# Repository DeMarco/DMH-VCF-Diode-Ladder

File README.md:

# DMH-VCF-Diode-Ladder

Voltage Controlled Filter module based on the design by Moritz Klein

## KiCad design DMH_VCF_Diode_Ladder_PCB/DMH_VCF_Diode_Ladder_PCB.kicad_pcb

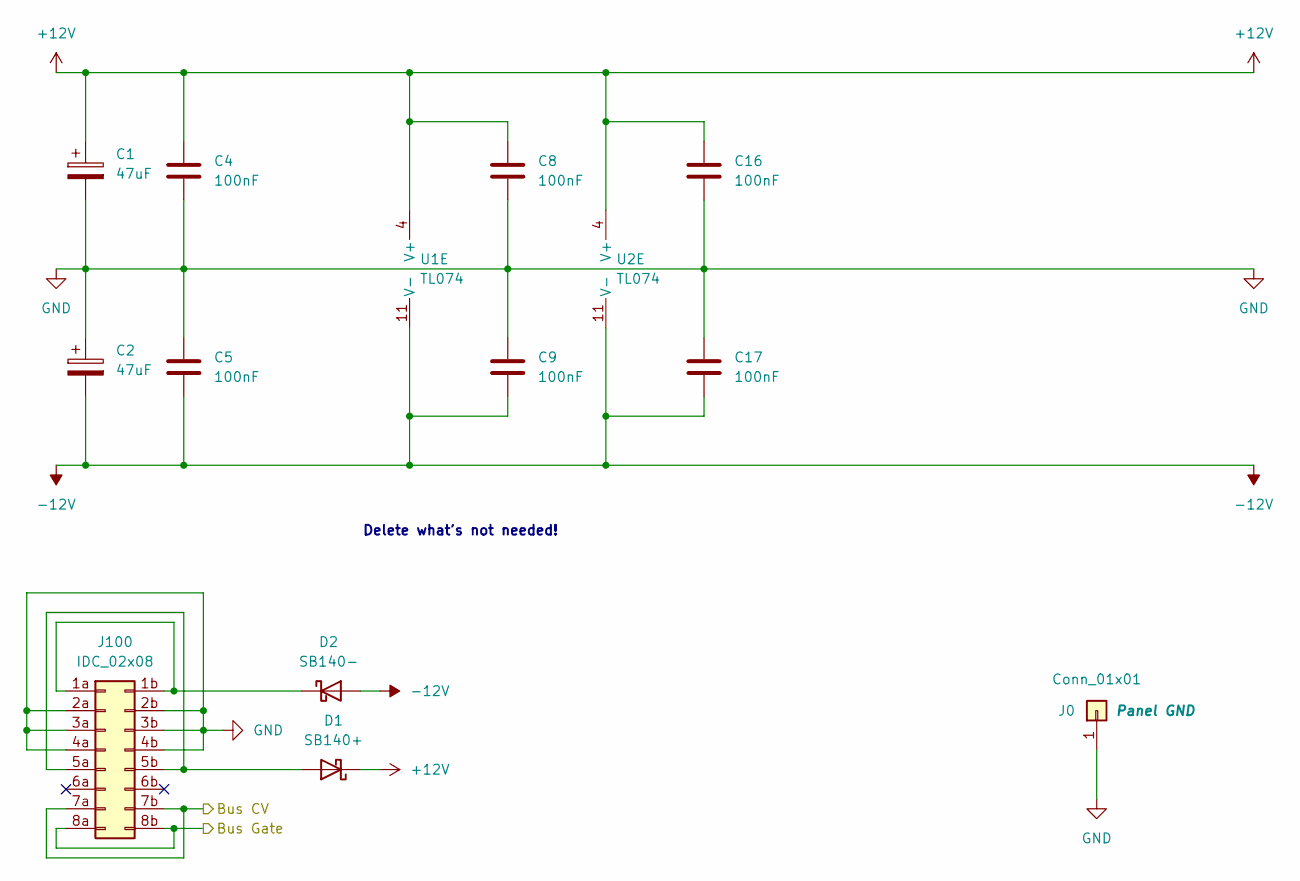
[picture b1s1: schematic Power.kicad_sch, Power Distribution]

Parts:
C1, C2: 47uF; CP_Radial_D5.0mm_P2.00mm
C4, C5, C8, C9, C16, C17: 100nF; C_Disc_D4.3mm_W1.9mm_P5.00mm
D1: SB140+; D_DO-41_SOD81_P10.16mm_Horizontal
D2: SB140-; D_DO-41_SOD81_P10.16mm_Horizontal
J0: Conn_01x01; PinHeader_1x01_P2.54mm_Vertical
J100: IDC_02x08; IDC-Header_2x08_P2.54mm_Vertical_Eurorack
U1, U2: TL074; DIP-14_W7.62mm_Socket

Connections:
+12V: C1.1, C4.1, C8.1, C16.1, D1.1 (K), U1.4 (V+), U2.4 (V+); also elsewhere on the board
-12V: C2.2, C5.2, C9.2, C17.2, D2.2 (A), U1.11 (V-), U2.11 (V-); also elsewhere on the board
/Inputs and Outputs/Bus CV In: J100.7a, J100.7b; also elsewhere on the board
/Power/Bus Gate: J100.8a, J100.8b
GND: C1.2, C2.1, C4.2, C5.1, C8.2, C9.1, C16.2, C17.1, J0.1, J100.2a, J100.2b, J100.3a, J100.3b, J100.4a, J100.4b; also elsewhere on the board
unnamed: D1.2 (A), J100.5a, J100.5b
unnamed: D2.1 (K), J100.1a, J100.1b

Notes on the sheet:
Delete what's not needed!

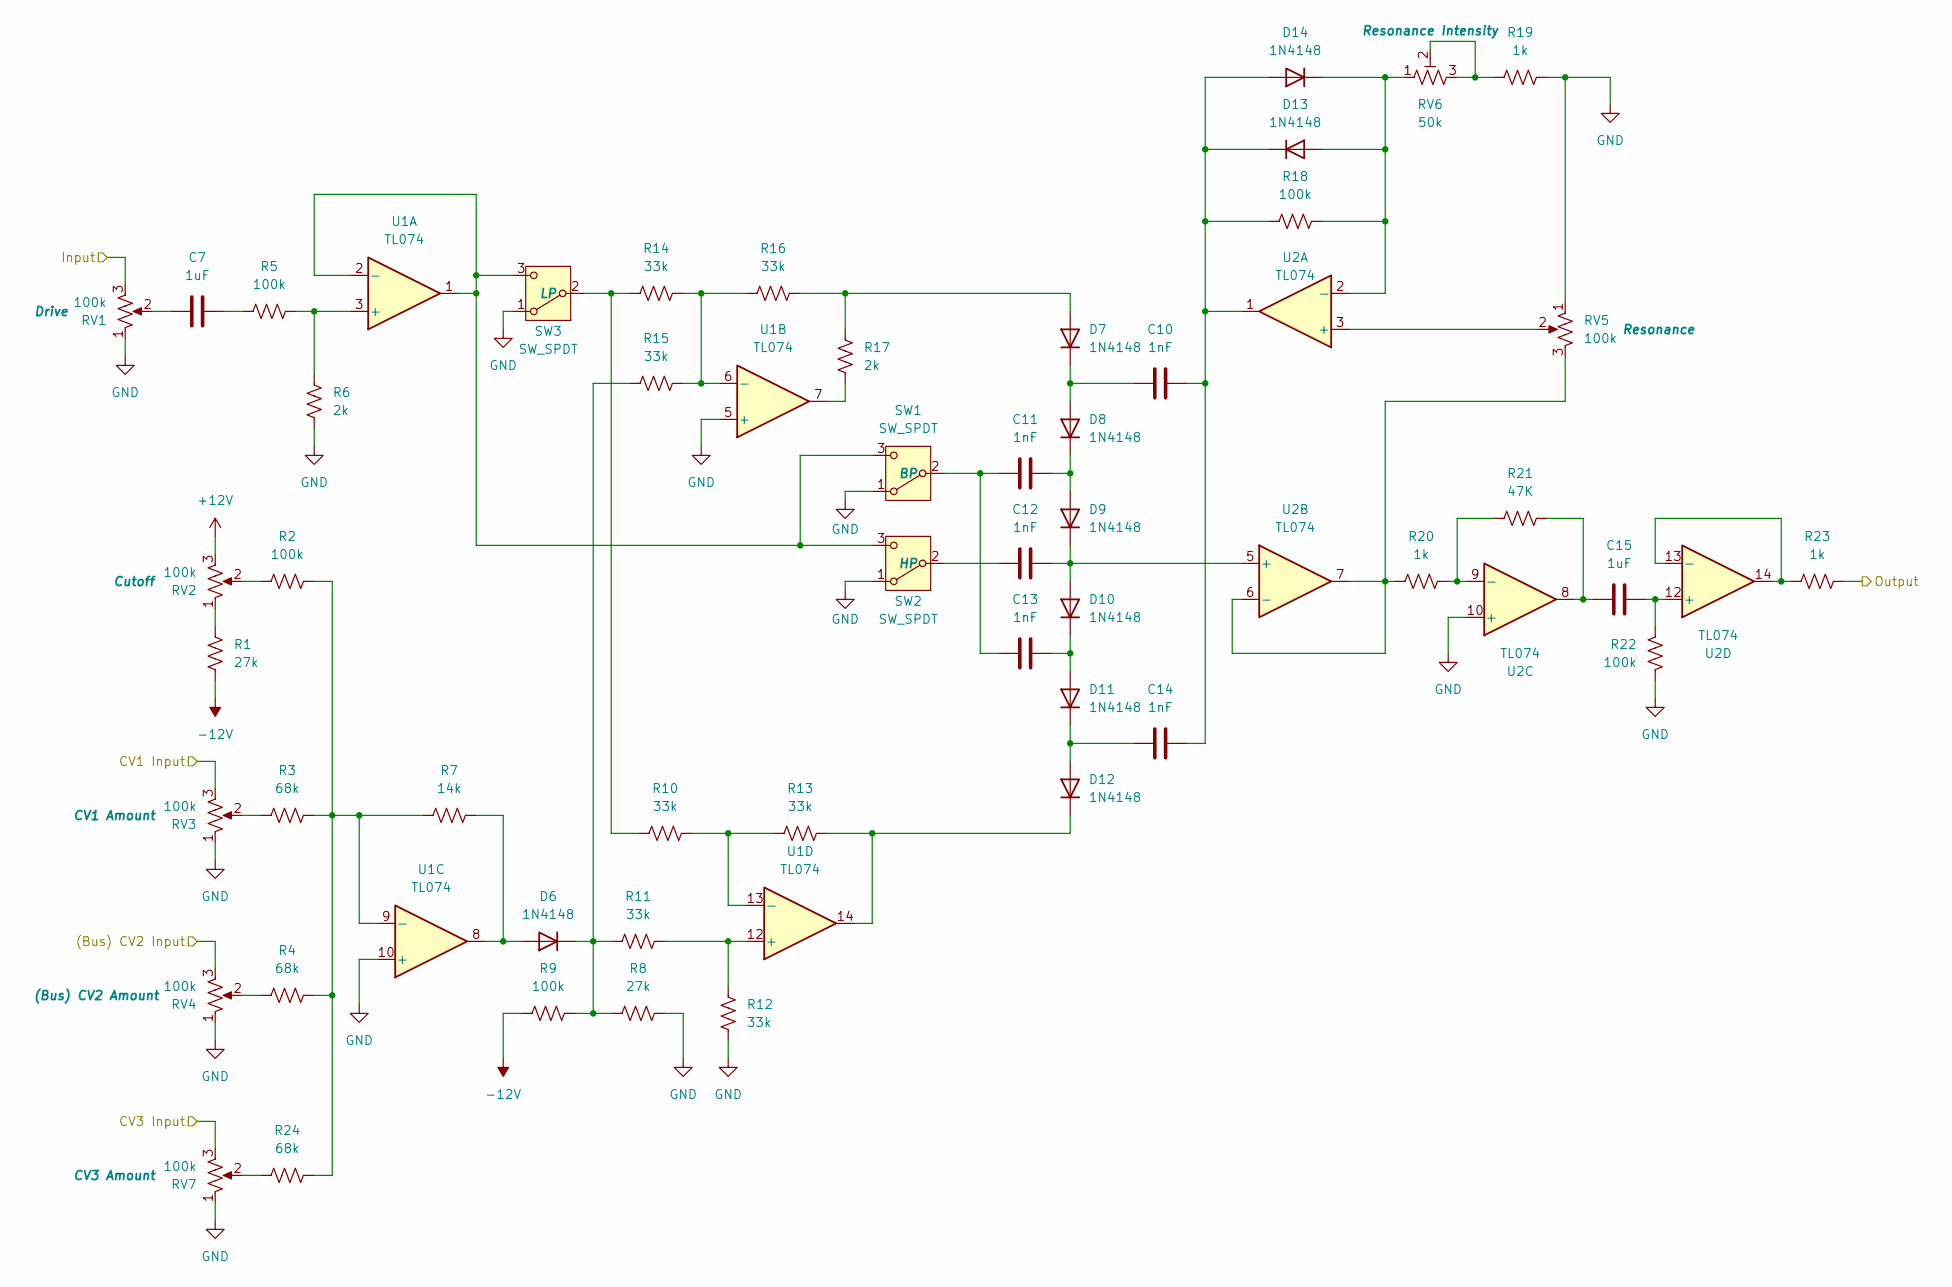
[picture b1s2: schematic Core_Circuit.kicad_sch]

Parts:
C7, C15: 1uF; C_Disc_D4.3mm_W1.9mm_P5.00mm
C10, C11, C12, C13, C14: 1nF; C_Disc_D4.3mm_W1.9mm_P5.00mm
D6, D7, D8, D9, D10, D11, D12, D13, D14: 1N4148; D_DO-35_SOD27_P7.62mm_Horizontal
R1, R8: 27k; R_Axial_DIN0207_L6.3mm_D2.5mm_P7.62mm_Horizontal
R2, R5, R9, R18, R22: 100k; R_Axial_DIN0207_L6.3mm_D2.5mm_P7.62mm_Horizontal
R3, R4, R24: 68k; R_Axial_DIN0207_L6.3mm_D2.5mm_P7.62mm_Horizontal
R6, R17: 2k; R_Axial_DIN0207_L6.3mm_D2.5mm_P7.62mm_Horizontal
R7: 14k; R_Axial_DIN0207_L6.3mm_D2.5mm_P7.62mm_Horizontal
R10, R11, R12, R13, R14, R15, R16: 33k; R_Axial_DIN0207_L6.3mm_D2.5mm_P7.62mm_Horizontal
R19, R20, R23: 1k; R_Axial_DIN0207_L6.3mm_D2.5mm_P7.62mm_Horizontal
R21: 47K; R_Axial_DIN0207_L6.3mm_D2.5mm_P7.62mm_Horizontal
RV1, RV2, RV3, RV4, RV5, RV7: 100k; Potentiometer_Alpha_RD901F-40-00D_Single_Vertical
RV6: 50k; Potentiometer_Bourns_3296W_Vertical
SW1, SW2, SW3: SW_SPDT; Toggle_Switch_THT
U1, U2: TL074; DIP-14_W7.62mm_Socket

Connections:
+12V: RV2.3; also elsewhere on the board
-12V: R1.2, R9.1; also elsewhere on the board
/Core Circuit/(Bus) CV2 Input: RV4.3; also elsewhere on the board
/Core Circuit/CV1 Input: RV3.3; also elsewhere on the board
/Core Circuit/CV3 Input: RV7.3; also elsewhere on the board
/Core Circuit/Input: RV1.3; also elsewhere on the board
/Core Circuit/Output: R23.2; also elsewhere on the board
GND: R6.1, R8.2, R12.1, R19.2, R22.1, RV1.1, RV3.1, RV4.1, RV5.1, RV7.1, SW1.1 (A), SW2.1 (A), SW3.1 (A), U1.5 (+), U1.10 (+), U2.10 (+); also elsewhere on the board
unnamed: C7.1, RV1.2
unnamed: C7.2, R5.1
unnamed: C15.1, R21.2, U2.8
unnamed: D6.2 (A), R7.2, U1.8
unnamed: D6.1 (K), R8.1, R9.2, R11.1, R15.1
unnamed: D7.2 (A), R16.2, R17.2
unnamed: C10.1, D7.1 (K), D8.2 (A)
unnamed: C11.2, D8.1 (K), D9.2 (A)
unnamed: C12.2, D9.1 (K), D10.2 (A), U2.5 (+)
unnamed: C13.2, D10.1 (K), D11.2 (A)
unnamed: C14.1, D11.1 (K), D12.2 (A)
unnamed: D12.1 (K), R13.2, U1.14
unnamed: D13.2 (A), D14.1 (K), R18.2, RV6.1, U2.2 (-)
unnamed: C10.2, C14.2, D13.1 (K), D14.2 (A), R18.1, U2.1
unnamed: R1.1, RV2.1
unnamed: R2.1, RV2.2
unnamed: R3.1, RV3.2
unnamed: R4.1, RV4.2
unnamed: R17.1, U1.7
unnamed: R19.1, RV6.2, RV6.3
unnamed: R24.1, RV7.2
unnamed: C11.1, C13.1, SW1.2 (B)
unnamed: SW1.3 (C), SW2.3 (C), SW3.3 (C), U1.1, U1.2 (-)
unnamed: C12.1, SW2.2 (B)
unnamed: R10.1, R14.1, SW3.2 (B)
unnamed: R5.2, R6.2, U1.3 (+)
unnamed: R14.2, R15.2, R16.1, U1.6 (-)
unnamed: R2.2, R3.2, R4.2, R7.1, R24.2, U1.9 (-)
unnamed: R11.2, R12.2, U1.12 (+)
unnamed: R10.2, R13.1, U1.13 (-)
unnamed: RV5.2, U2.3 (+)
unnamed: R20.1, RV5.3, U2.6 (-), U2.7
unnamed: R20.2, R21.1, U2.9 (-)
unnamed: C15.2, R22.2, U2.12 (+)
unnamed: R23.1, U2.13 (-), U2.14

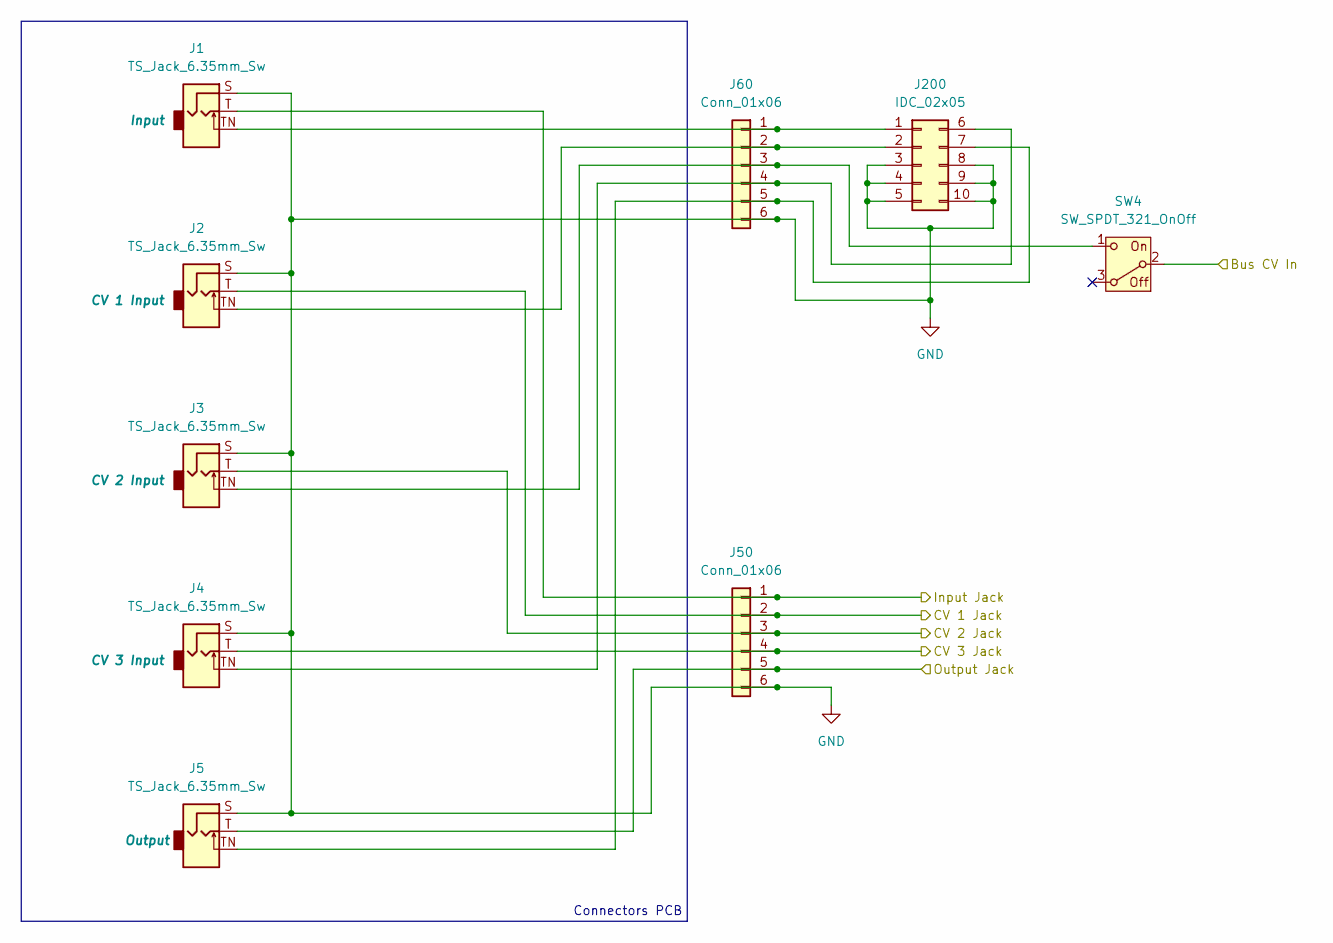
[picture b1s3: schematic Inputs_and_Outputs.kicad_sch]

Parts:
J1, J2, J3, J4, J5: TS_Jack_6.35mm_Sw; CUI_MJ-63052A
J50, J60: Conn_01x06; PinSocket_1x06_P2.54mm_Vertical
J200: IDC_02x05; IDC-Header_2x05_P2.54mm_Vertical_BackBone
SW4: SW_SPDT_321_OnOff; Toggle_Switch_THT

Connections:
/Core Circuit/(Bus) CV2 Input: J3.T, J50.3; also elsewhere on the board
/Core Circuit/CV1 Input: J2.T, J50.2; also elsewhere on the board
/Core Circuit/CV3 Input: J4.T, J50.4; also elsewhere on the board
/Core Circuit/Input: J1.T, J50.1; also elsewhere on the board
/Core Circuit/Output: J5.T, J50.5; also elsewhere on the board
/Inputs and Outputs/Bus CV In: SW4.2 (B); also elsewhere on the board
GND: J1.S, J2.S, J3.S, J4.S, J5.S, J50.6, J60.6, J200.3, J200.4, J200.5, J200.8, J200.9, J200.10; also elsewhere on the board
unnamed: J3.TN, J60.3, SW4.1 (C)
unnamed: J1.TN, J60.1, J200.1
unnamed: J2.TN, J60.2, J200.2
unnamed: J4.TN, J60.4, J200.6
unnamed: J5.TN, J60.5, J200.7

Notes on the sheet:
Connectors PCB

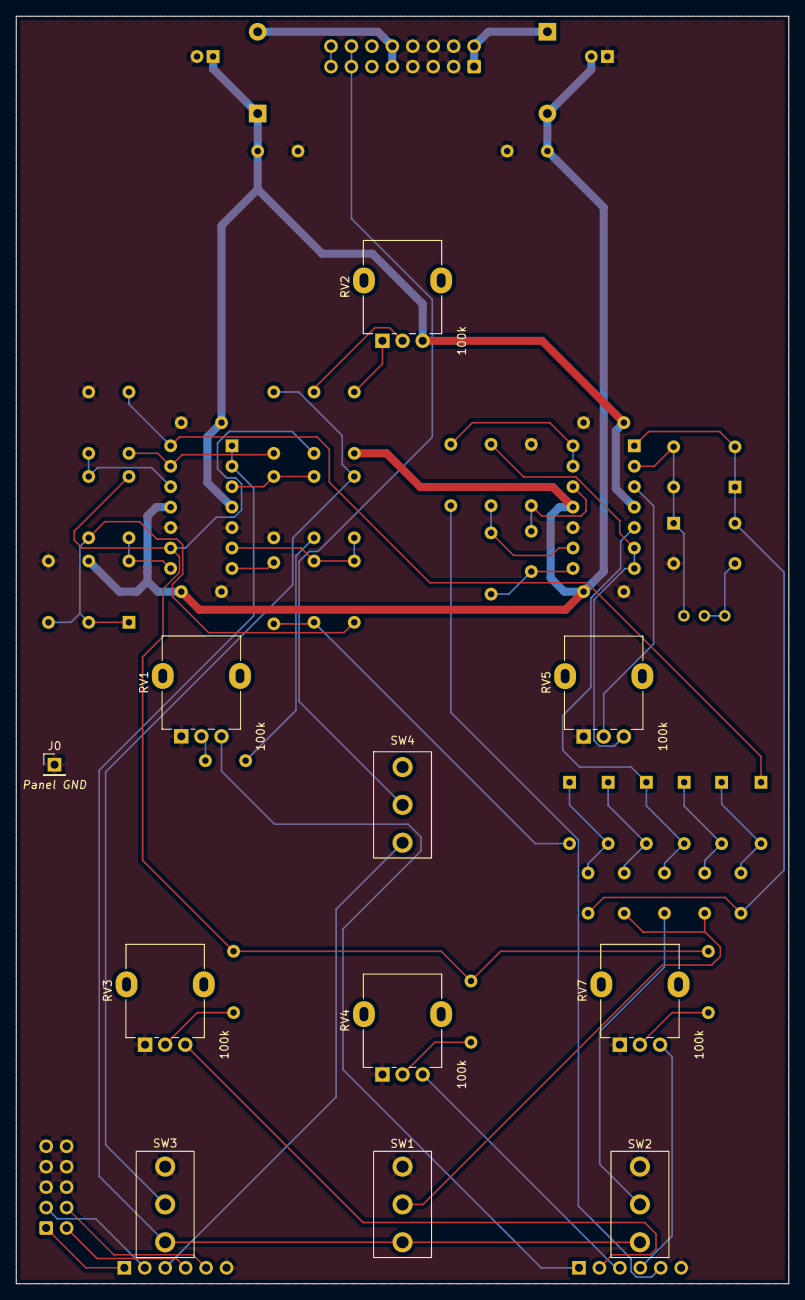
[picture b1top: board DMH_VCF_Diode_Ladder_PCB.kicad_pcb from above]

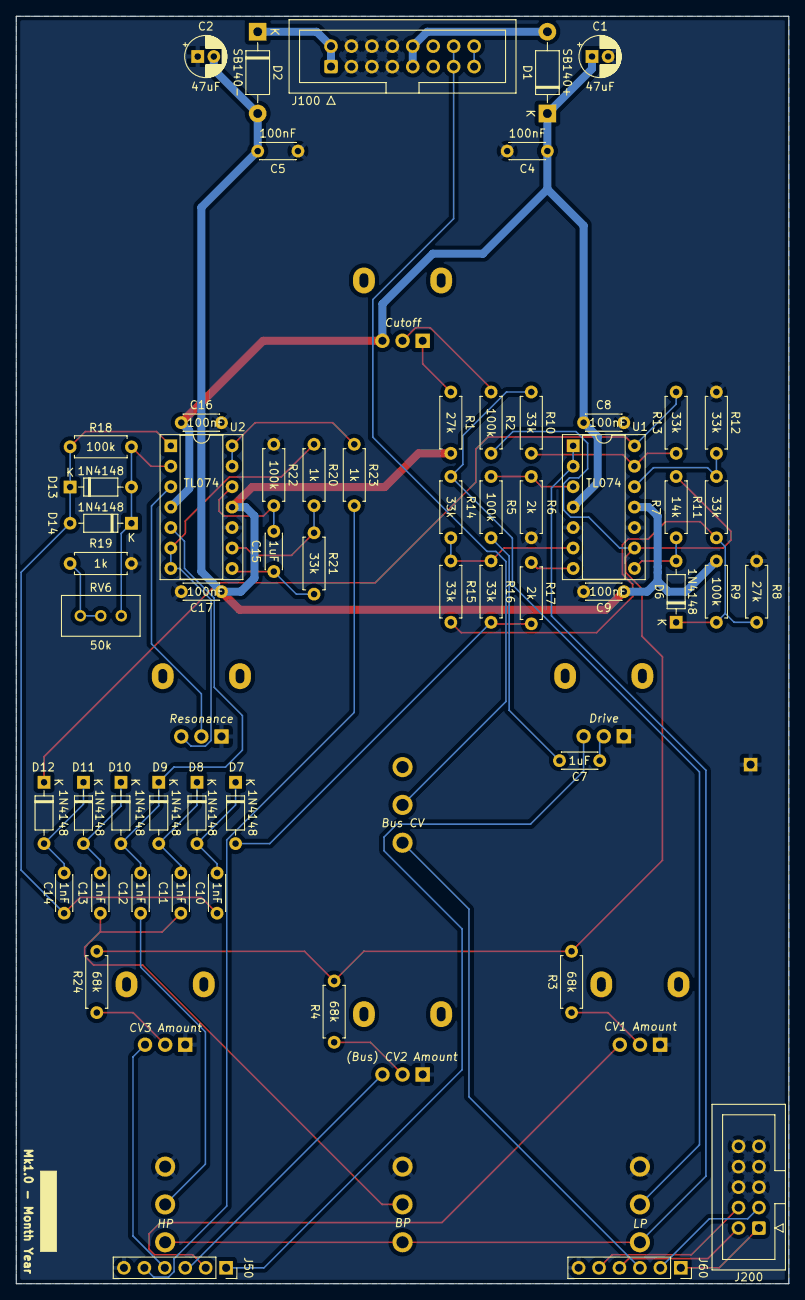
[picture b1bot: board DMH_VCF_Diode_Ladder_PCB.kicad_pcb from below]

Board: 2 copper layers, 96.0 x 157.5 mm, 68 parts (57 on the bottom side), 52 nets.

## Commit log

2024-09-17 Updated readme and gitignore
2024-09-17 Created panel KiCad project
2024-09-17 Created PCB KiCad project
2024-09-18 Designed front panel
2024-09-20 Sync lib
2024-09-20 Main schematic in progress
2024-09-20 Finished schematic and added Bus CV 2 pot
2024-09-21 Added Bus CV On Off switch
2024-09-22 Added tiny knob 3d model
2024-09-22 Added panel component 3D models
2024-09-22 Sync libs
2024-09-22 Component placement in progress
2024-09-23 Component placement done
2024-09-23 Routing in progress
2024-09-23 Update SynthStuff
2024-09-23 Main PCB routing done
2024-09-23 Created Connectors PCB project
2024-09-23 Finished connectors PCB
2024-11-05 Increased output stage gain to x47
2025-02-23 Converted to KiCad 9
2025-03-02 Changed cutoff pot limiting resistances in sch
